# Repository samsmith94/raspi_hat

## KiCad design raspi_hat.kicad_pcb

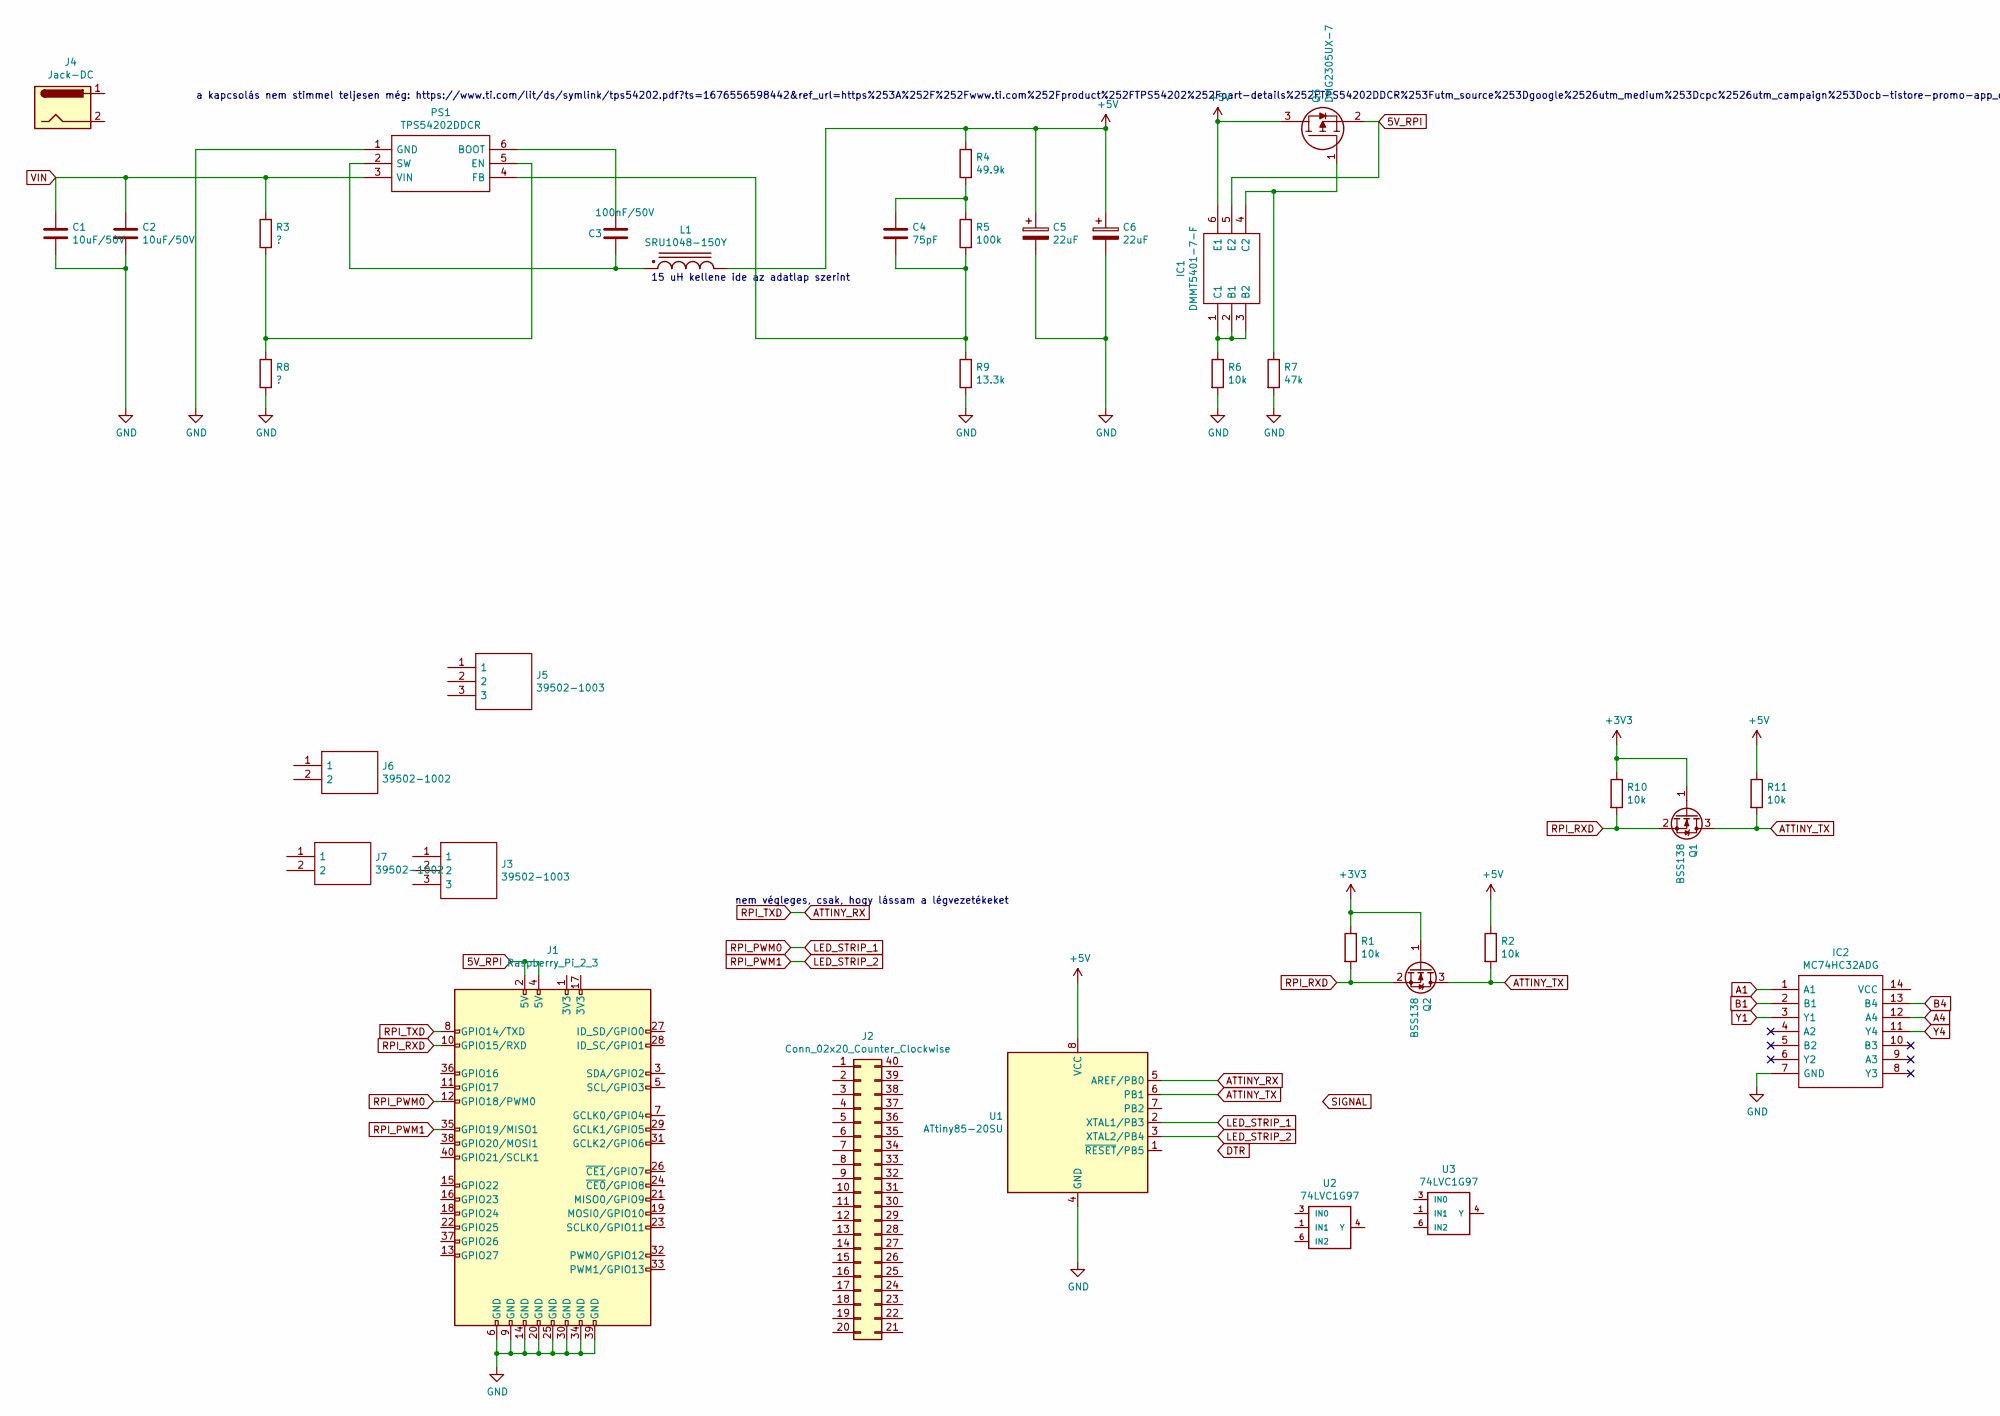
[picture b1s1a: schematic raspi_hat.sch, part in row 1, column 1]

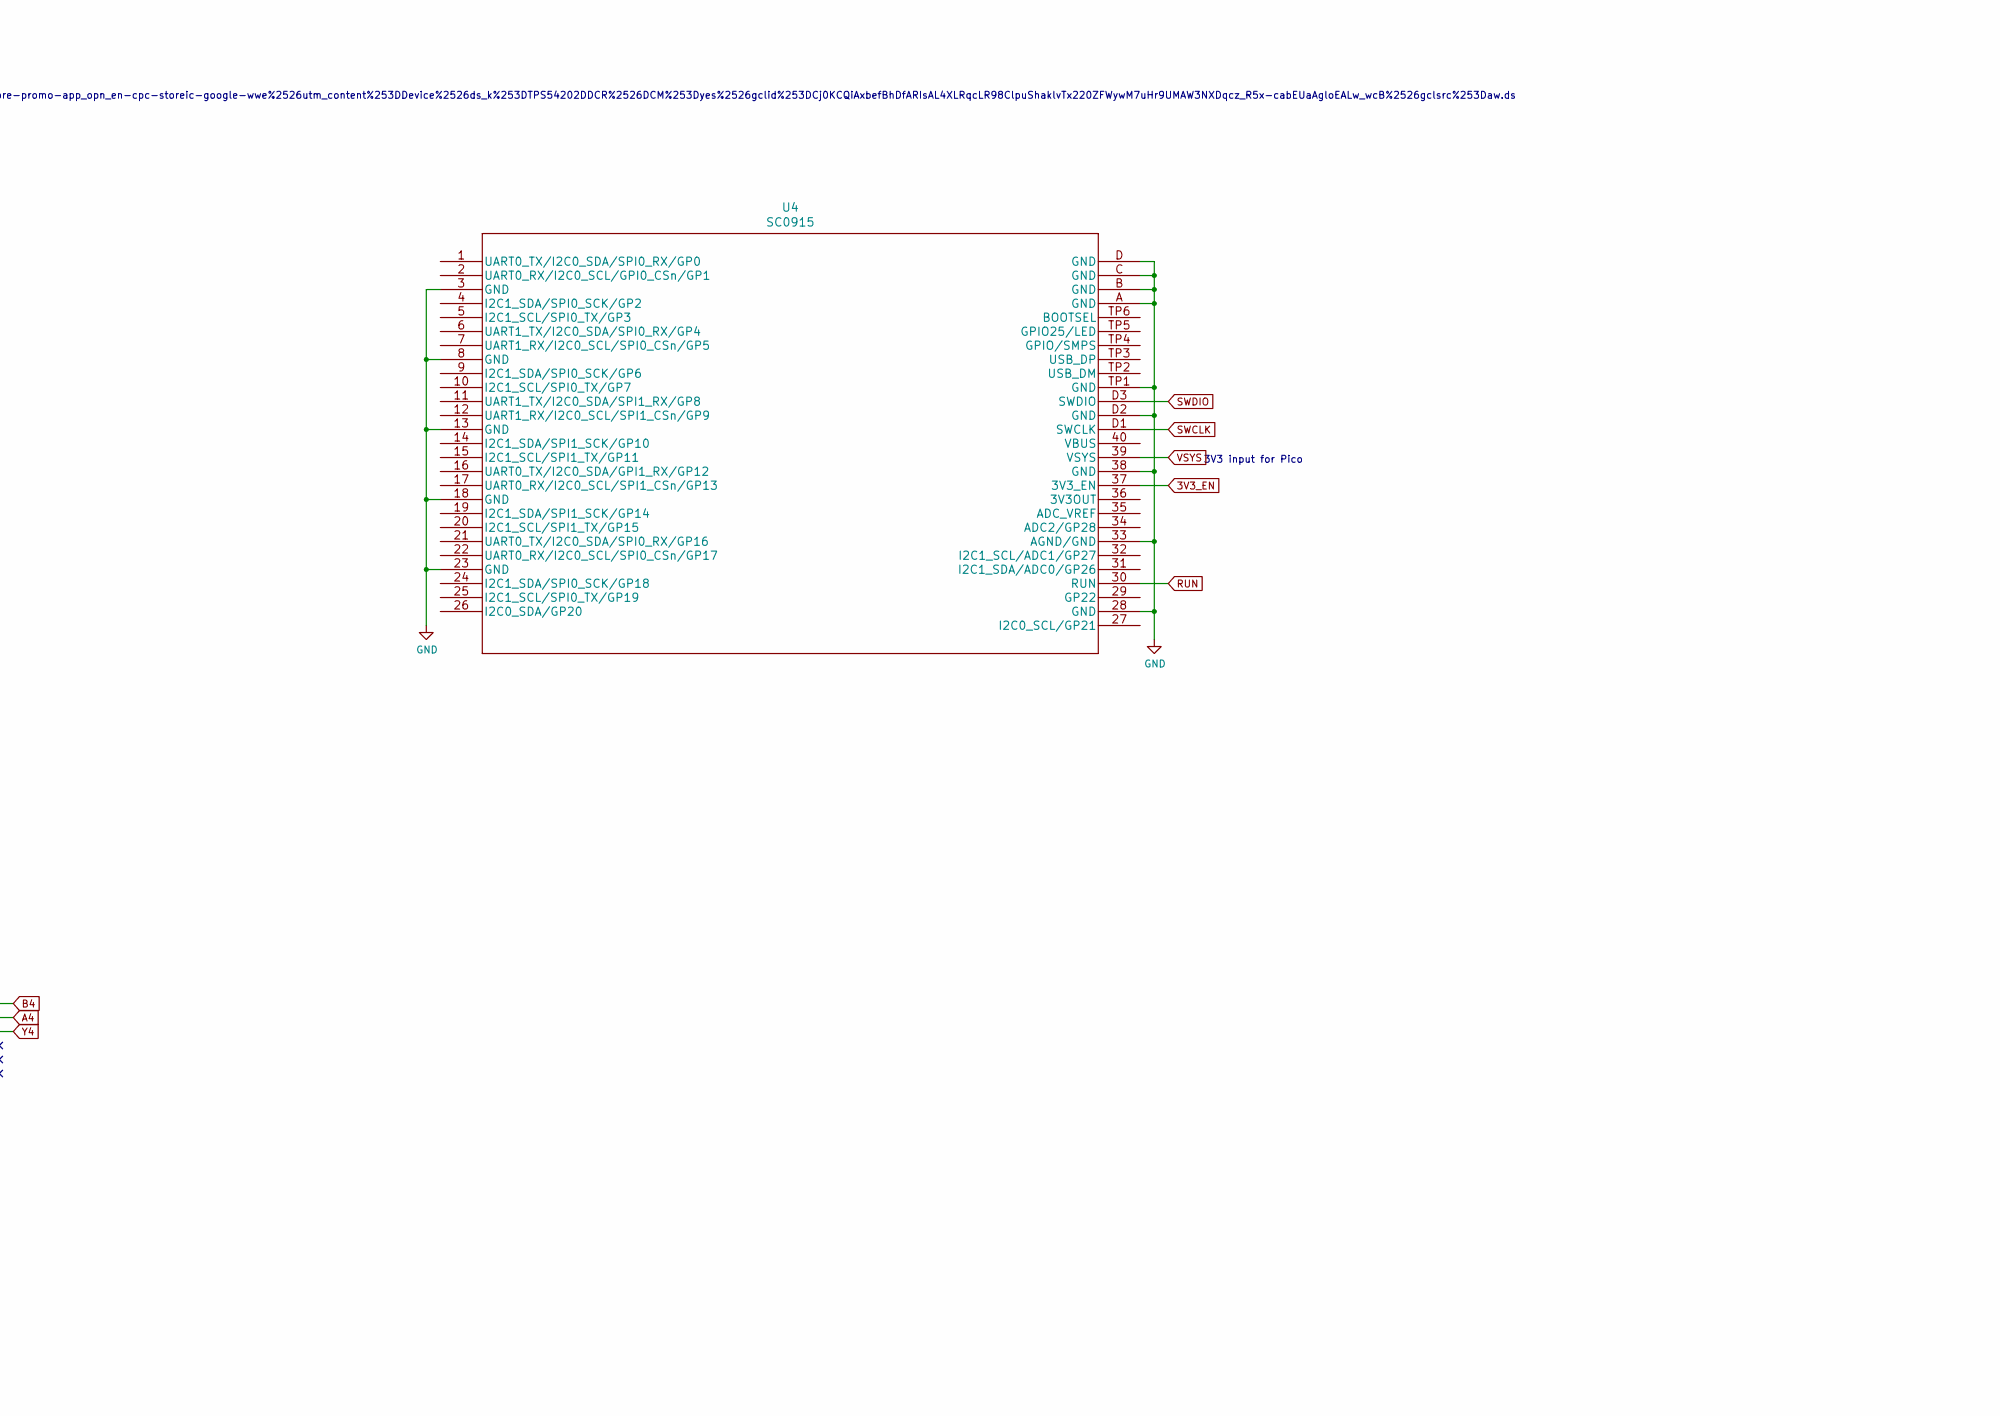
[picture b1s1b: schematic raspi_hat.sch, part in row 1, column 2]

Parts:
C1, C2: 10uF/50V; C_1206_3216Metric_Pad1.33x1.80mm_HandSolder
C3: 100nF/50V; C_0603_1608Metric_Pad1.08x0.95mm_HandSolder
C4: 75pF; C_0603_1608Metric_Pad1.08x0.95mm_HandSolder
C5, C6: 22uF; C_1206_3216Metric_Pad1.33x1.80mm_HandSolder
IC1: DMMT5401-7-F; Manufacturer_Part_Number DMMT5401-7-F; Mouser Part Number 621-DMMT5401-7-F
IC2: MC74HC32ADG; Manufacturer_Part_Number MC74HC32ADG; Mouser Part Number 863-MC74HC32ADG
J1: Raspberry_Pi_2_3; raspberrypi_2_3
J2: Conn_02x20_Counter_Clockwise; PinHeader_2x20_P2.54mm_Vertical
J3, J5: 39502-1003; Manufacturer_Part_Number 39502-1003; Mouser Part Number 538-39502-1003
J4: Jack-DC; BarrelJack_Horizontal
J6, J7: 39502-1002; Manufacturer_Part_Number 39502-1002; Mouser Part Number 538-39502-1002
L1: SRU1048-150Y; PARTREV 03/18
PS1: TPS54202DDCR; Manufacturer_Part_Number TPS54202DDCR; Mouser Part Number 595-TPS54202DDCR
Q1, Q2: BSS138; SOT-23
Q3: DMG2305UX-7; Manufacturer_Part_Number DMG2305UX-7; Mouser Part Number 621-DMG2305UX-7
R1, R2, R6, R10, R11: 10k; R_0805_2012Metric_Pad1.20x1.40mm_HandSolder
R3, R8: ?; R_0603_1608Metric_Pad0.98x0.95mm_HandSolder
R4: 49.9k; R_0603_1608Metric_Pad0.98x0.95mm_HandSolder
R5: 100k; R_0603_1608Metric_Pad0.98x0.95mm_HandSolder
R7: 47k; R_0805_2012Metric_Pad1.20x1.40mm_HandSolder
R9: 13.3k; R_0603_1608Metric_Pad0.98x0.95mm_HandSolder
U1: ATtiny85-20SU; SOIJ-8_5.3x5.3mm_P1.27mm
U2, U3: 74LVC1G97; SOT-363_SC-70-6_Handsoldering
U4: SC0915; raspberry-pi-pico-r3-1

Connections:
3V3_EN: U4.37 (3V3_EN)
5V_RPI: IC1.5 (E2), J1.2 (5V), J1.4 (5V), Q3.2
+3V3: Q1.1 (G), Q2.1 (G), R1.1, R10.1
+5V: C5.1, C6.1, IC1.6 (E1), L1.2, Q3.3, R2.1, R4.2, R11.1, U1.8 (VCC)
A1: IC2.1 (A1)
A4: IC2.12 (A4)
ATTINY_RX: J1.8 (GPIO14/TXD), U1.5 (AREF/PB0)
ATTINY_TX: Q1.3 (D), Q2.3 (D), R2.2, R11.2, U1.6 (PB1)
B1: IC2.2 (B1)
B4: IC2.13 (B4)
GND: C1.2, C2.2, C5.2, C6.2, IC2.7 (GND), J1.6 (GND), J1.9 (GND), J1.14 (GND), J1.20 (GND), J1.25 (GND), J1.30 (GND), J1.34 (GND), J1.39 (GND), PS1.1 (GND), R6.2, R7.2, R8.1, R9.1, U1.4 (GND), U2.2 (GND), U3.2 (GND), U4.3 (GND), U4.8 (GND), U4.13 (GND), U4.18 (GND), U4.23 (GND), U4.28 (GND), U4.33 (AGND/GND), U4.38 (GND), U4.A (GND), U4.B (GND), U4.C (GND), U4.D (GND), U4.D2 (GND), U4.TP1 (GND)
LED_STRIP_1: J1.12 (GPIO18/PWM0), U1.2 (XTAL1/PB3)
LED_STRIP_2: J1.35 (GPIO19/MISO1), U1.3 (XTAL2/PB4)
unnamed: C3.1, PS1.6 (BOOT)
unnamed: C3.2, L1.1, PS1.2 (SW)
unnamed: C4.1, R4.1, R5.2
unnamed: C4.2, PS1.4 (FB), R5.1, R9.2
unnamed: IC1.1 (C1), IC1.2 (B1), IC1.3 (B2), R6.1
unnamed: IC1.4 (C2), Q3.1, R7.1
unnamed: PS1.5 (EN), R3.1, R8.2
RPI_RXD: J1.10 (GPIO15/RXD), Q1.2 (S), Q2.2 (S), R1.2, R10.2
RUN: U4.30 (RUN)
SWCLK: U4.D1 (SWCLK)
SWDIO: U4.D3 (SWDIO)
VCC: U2.5 (VCC), U3.5 (VCC)
VIN: C1.1, C2.1, PS1.3 (VIN), R3.2
VSYS: U4.39 (VSYS)
Y1: IC2.3 (Y1)
Y4: IC2.11 (Y4)

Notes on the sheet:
nem végleges, csak, hogy lássam a légvezetékeket
a kapcsolás nem stimmel teljesen még: https://www.ti.com/lit/ds/symlink/tps54202.pdf?ts=1676556598442&ref_url=https%253A%252F%252Fwww.ti.com%252Fproduct%252FTPS54202%252Fpart-details%252FTPS54202DDCR%253Futm_source%253Dgoogle%2526utm_medium%253Dcpc%2526utm_campaign%253Docb-tistore-promo-app_opn_en-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
15 uH kellene ide az adatlap szerint
3V3 input for Pico

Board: 2 copper layers, 35 parts (1 on the bottom side), 18 nets, no tracks yet.

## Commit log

2023-02-09 add power parts
2023-02-14 power save
2023-02-18 big save before Pico

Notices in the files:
parts and their libraries:
Copyright 2021 Accelerated Designs. All rights reserved.
